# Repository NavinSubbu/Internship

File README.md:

# Internship

A simple code and circuit to convert 5v to 3.3v and 3.3v to 1v using Arduino and Python

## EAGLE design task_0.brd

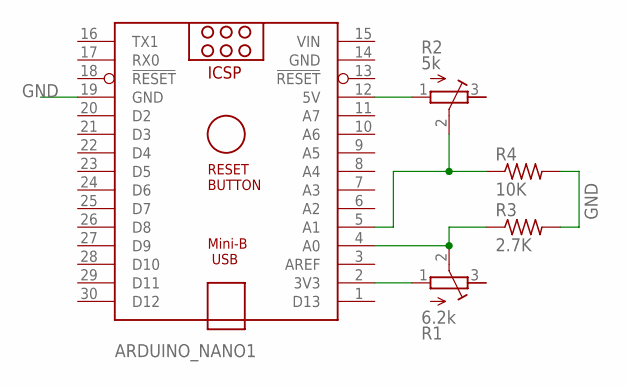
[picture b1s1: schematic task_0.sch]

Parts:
ARDUINO_NANO1: ARDUINO_NANO
R1: 6.2k; RTRIM3296W
R2: 5k; RTRIM3296W
R3: 2.7K; 0204/7
R4: 10K; 0204/7

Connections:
GND: ARDUINO_NANO1.14 (GND), ARDUINO_NANO1.19 (GND), R3.2, R4.2
unnamed: ARDUINO_NANO1.5 (A1), R2.2 (S), R4.1
unnamed: ARDUINO_NANO1.12 (5V), R2.1 (A)
unnamed: ARDUINO_NANO1.2 (3V3), R1.1 (A)
unnamed: ARDUINO_NANO1.4 (A0), R1.2 (S), R3.1
VIN: ARDUINO_NANO1.15 (VIN)

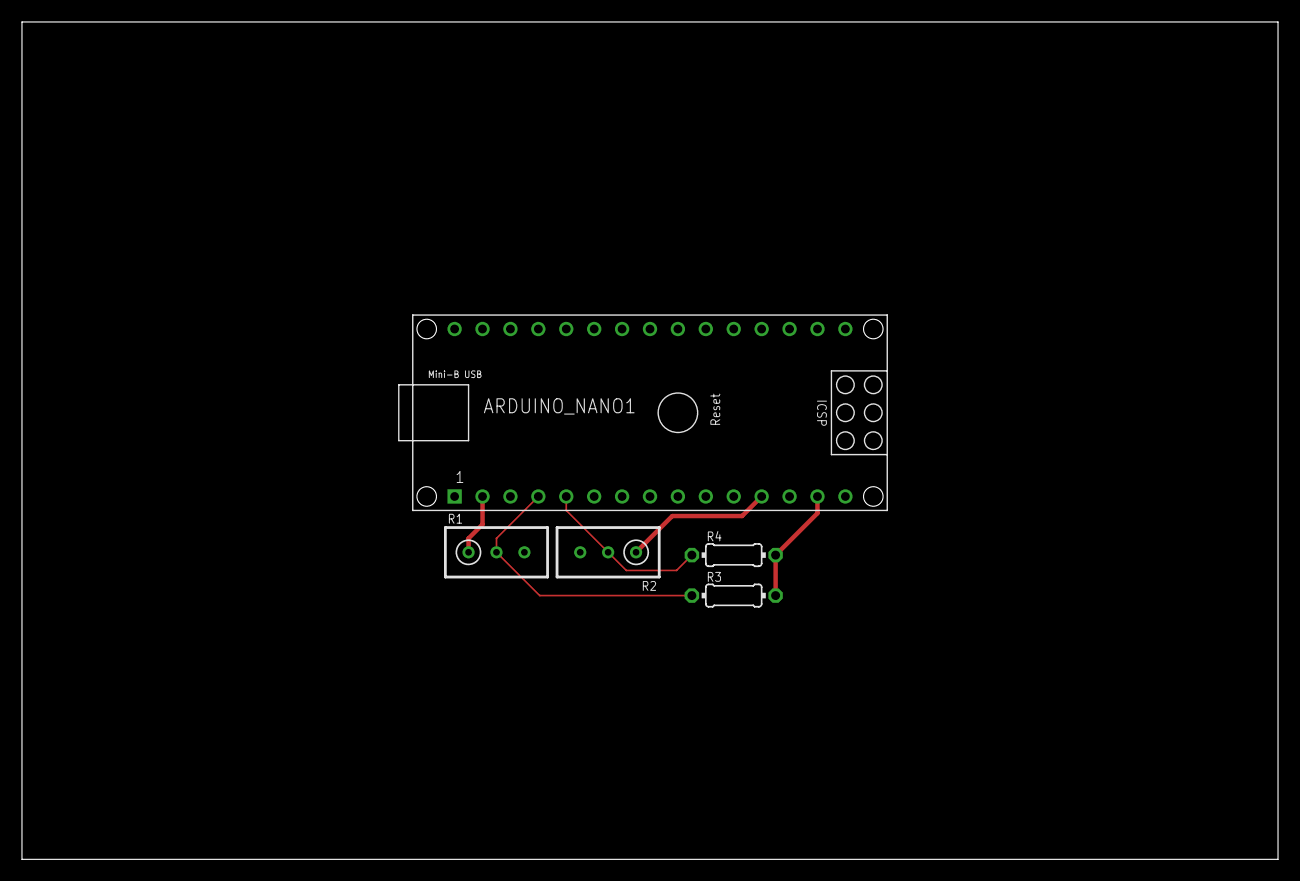
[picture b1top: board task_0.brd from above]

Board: 2 copper layers, 114.3 x 76.2 mm, 5 parts (0 on the bottom side), 5 nets.
